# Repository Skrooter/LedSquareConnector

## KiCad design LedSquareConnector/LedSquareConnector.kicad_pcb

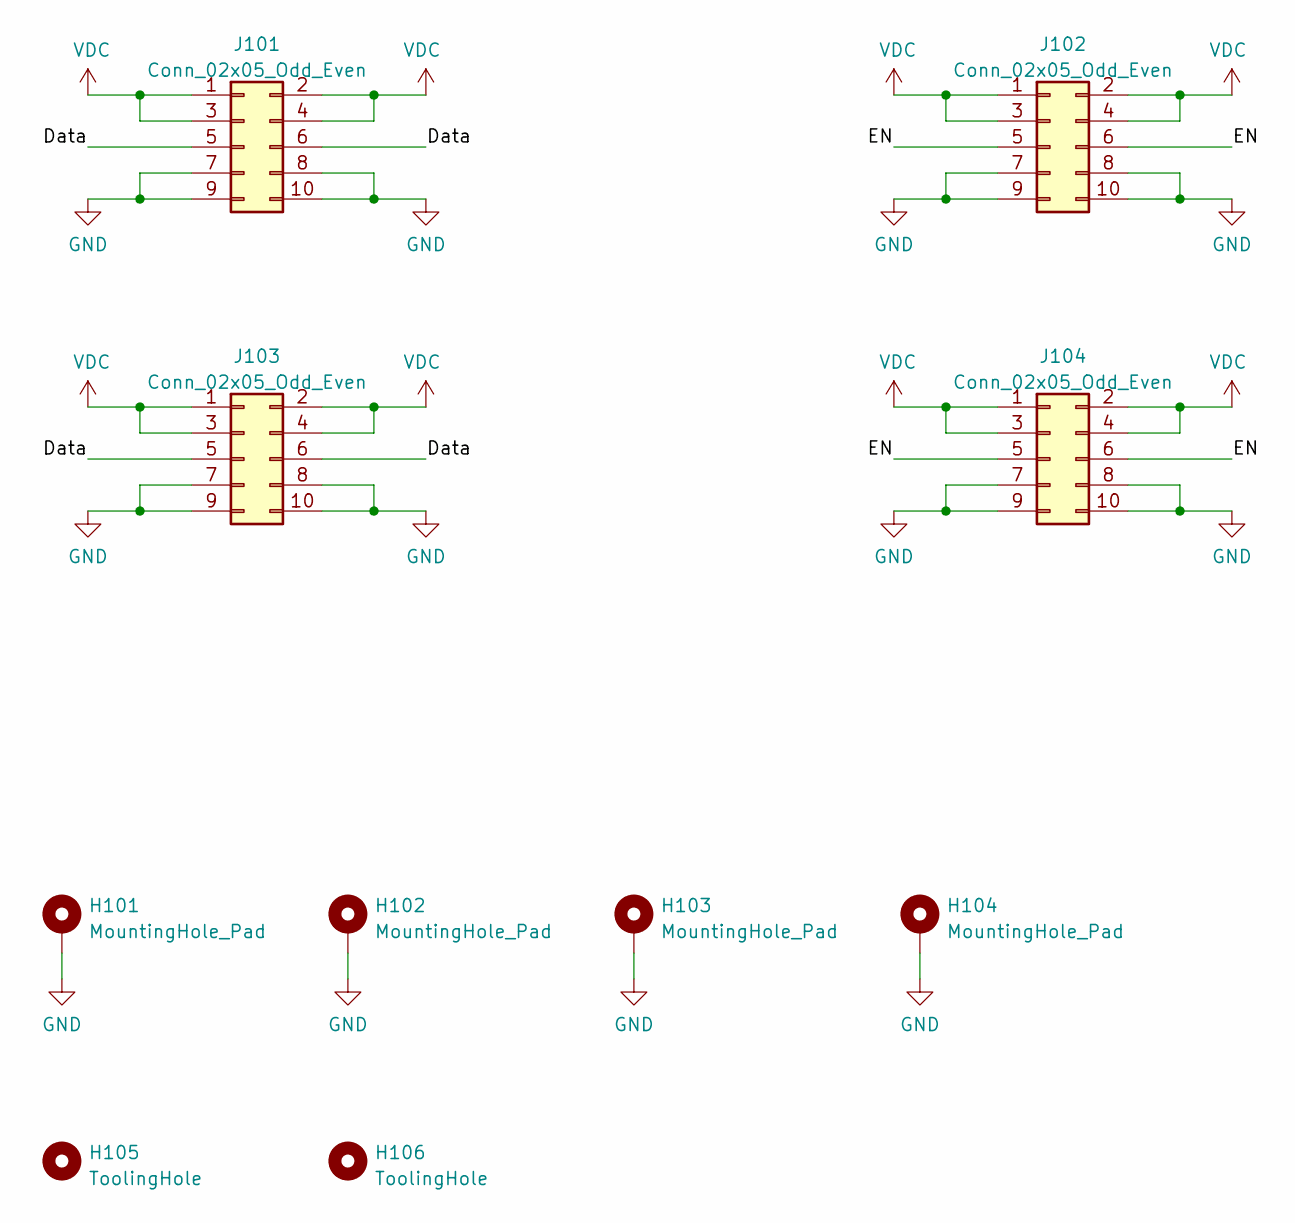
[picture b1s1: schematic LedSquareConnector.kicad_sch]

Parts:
H101, H102, H103, H104: MountingHole_Pad; MountingHole_5.3mm_M5_Pad_Via
H105, H106: ToolingHole; JLC_toolinghole
J101, J102, J103, J104: Conn_02x05_Odd_Even; PinHeader_2x05_P2.54mm_Vertical; LCSC C492422

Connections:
/Data: J101.5, J101.6, J103.5, J103.6
/EN: J102.5, J102.6, J104.5, J104.6
GND: H101.1, H102.1, H103.1, H104.1, J101.7, J101.8, J101.9, J101.10, J102.7, J102.8, J102.9, J102.10, J103.7, J103.8, J103.9, J103.10, J104.7, J104.8, J104.9, J104.10
VDC: J101.1, J101.2, J101.3, J101.4, J102.1, J102.2, J102.3, J102.4, J103.1, J103.2, J103.3, J103.4, J104.1, J104.2, J104.3, J104.4

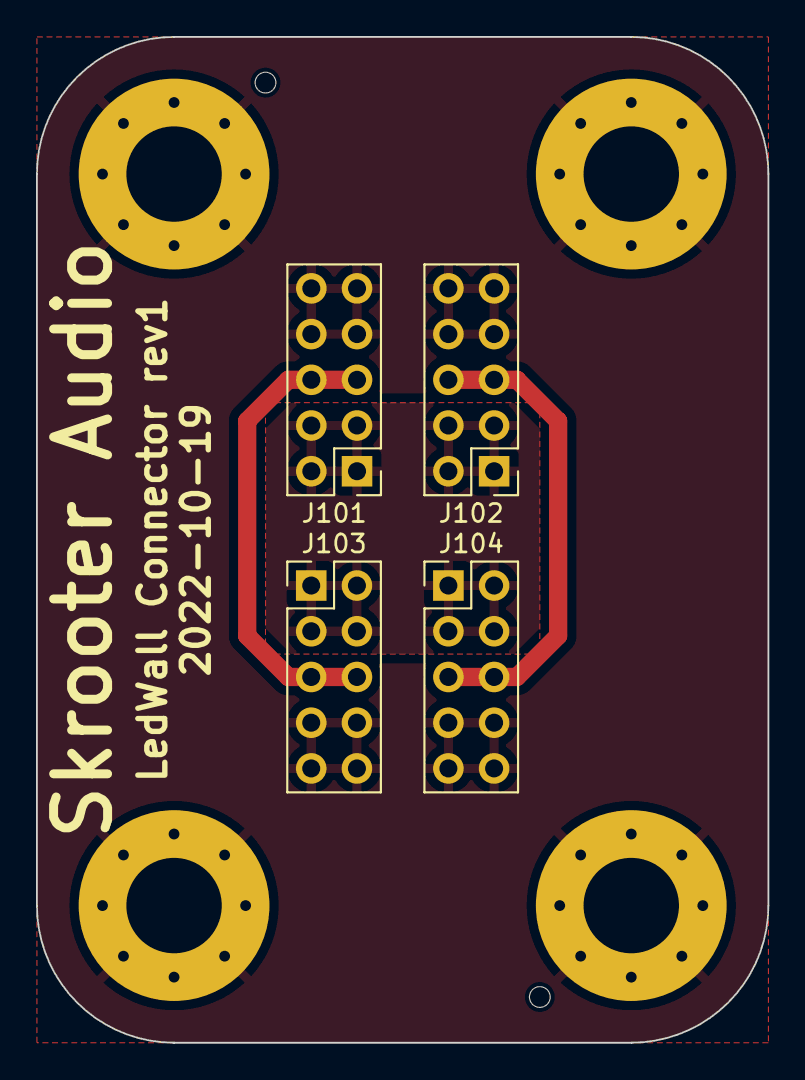
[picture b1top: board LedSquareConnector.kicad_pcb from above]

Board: 2 copper layers, 40.6 x 55.9 mm, 10 parts (0 on the bottom side), 4 nets.

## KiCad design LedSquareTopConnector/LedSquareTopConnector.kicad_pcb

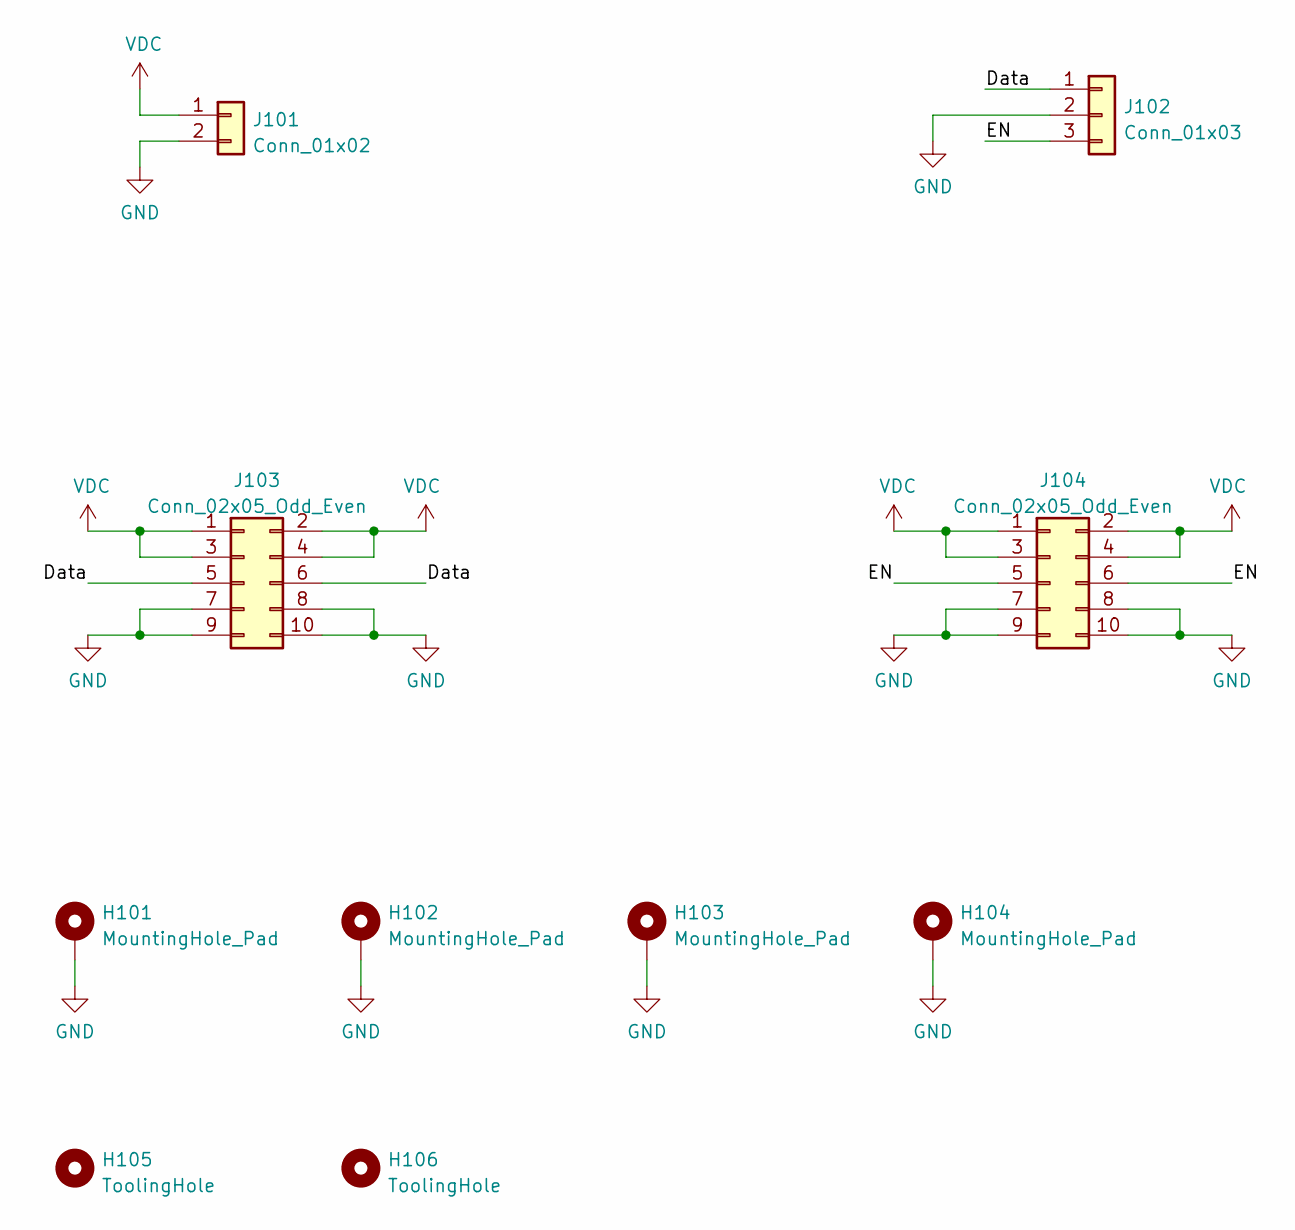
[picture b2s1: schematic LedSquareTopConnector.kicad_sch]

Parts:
H101, H102, H103, H104: MountingHole_Pad; MountingHole_5.3mm_M5_Pad_Via
H105, H106: ToolingHole; JLC_toolinghole
J101: Conn_01x02; PhoenixContact_MC_1,5_2-G-3.81_1x02_P3.81mm_Horizontal
J102: Conn_01x03; PhoenixContact_MC_1,5_3-G-3.81_1x03_P3.81mm_Horizontal
J103, J104: Conn_02x05_Odd_Even; PinHeader_2x05_P2.54mm_Vertical; LCSC C492422

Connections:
/Data: J102.1, J103.5, J103.6
/EN: J102.3, J104.5, J104.6
GND: H101.1, H102.1, H103.1, H104.1, J101.2, J102.2, J103.7, J103.8, J103.9, J103.10, J104.7, J104.8, J104.9, J104.10
VDC: J101.1, J103.1, J103.2, J103.3, J103.4, J104.1, J104.2, J104.3, J104.4

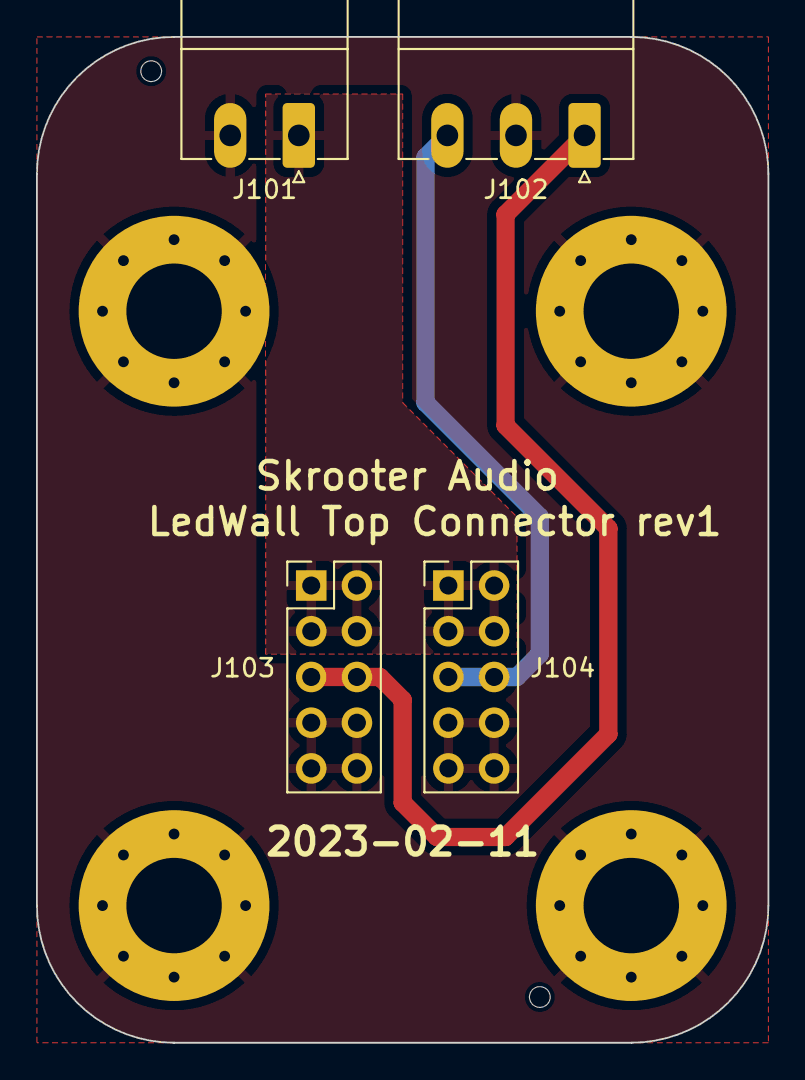
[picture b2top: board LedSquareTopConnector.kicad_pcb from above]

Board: 2 copper layers, 40.6 x 55.9 mm, 10 parts (0 on the bottom side), 4 nets.

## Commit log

2022-10-19 Inital commit with rev1 of PCB
2023-02-11 Change connector and prep for manufactoring
2023-03-11 Revert last commit and move upper header 50 mil
2023-03-11 Add LCSC partnumbers to headers
2023-03-11 fix many small issues
2023-03-11 Move files to subfolder
2023-03-11 Add top connector
2023-04-14 Final fixes before production
